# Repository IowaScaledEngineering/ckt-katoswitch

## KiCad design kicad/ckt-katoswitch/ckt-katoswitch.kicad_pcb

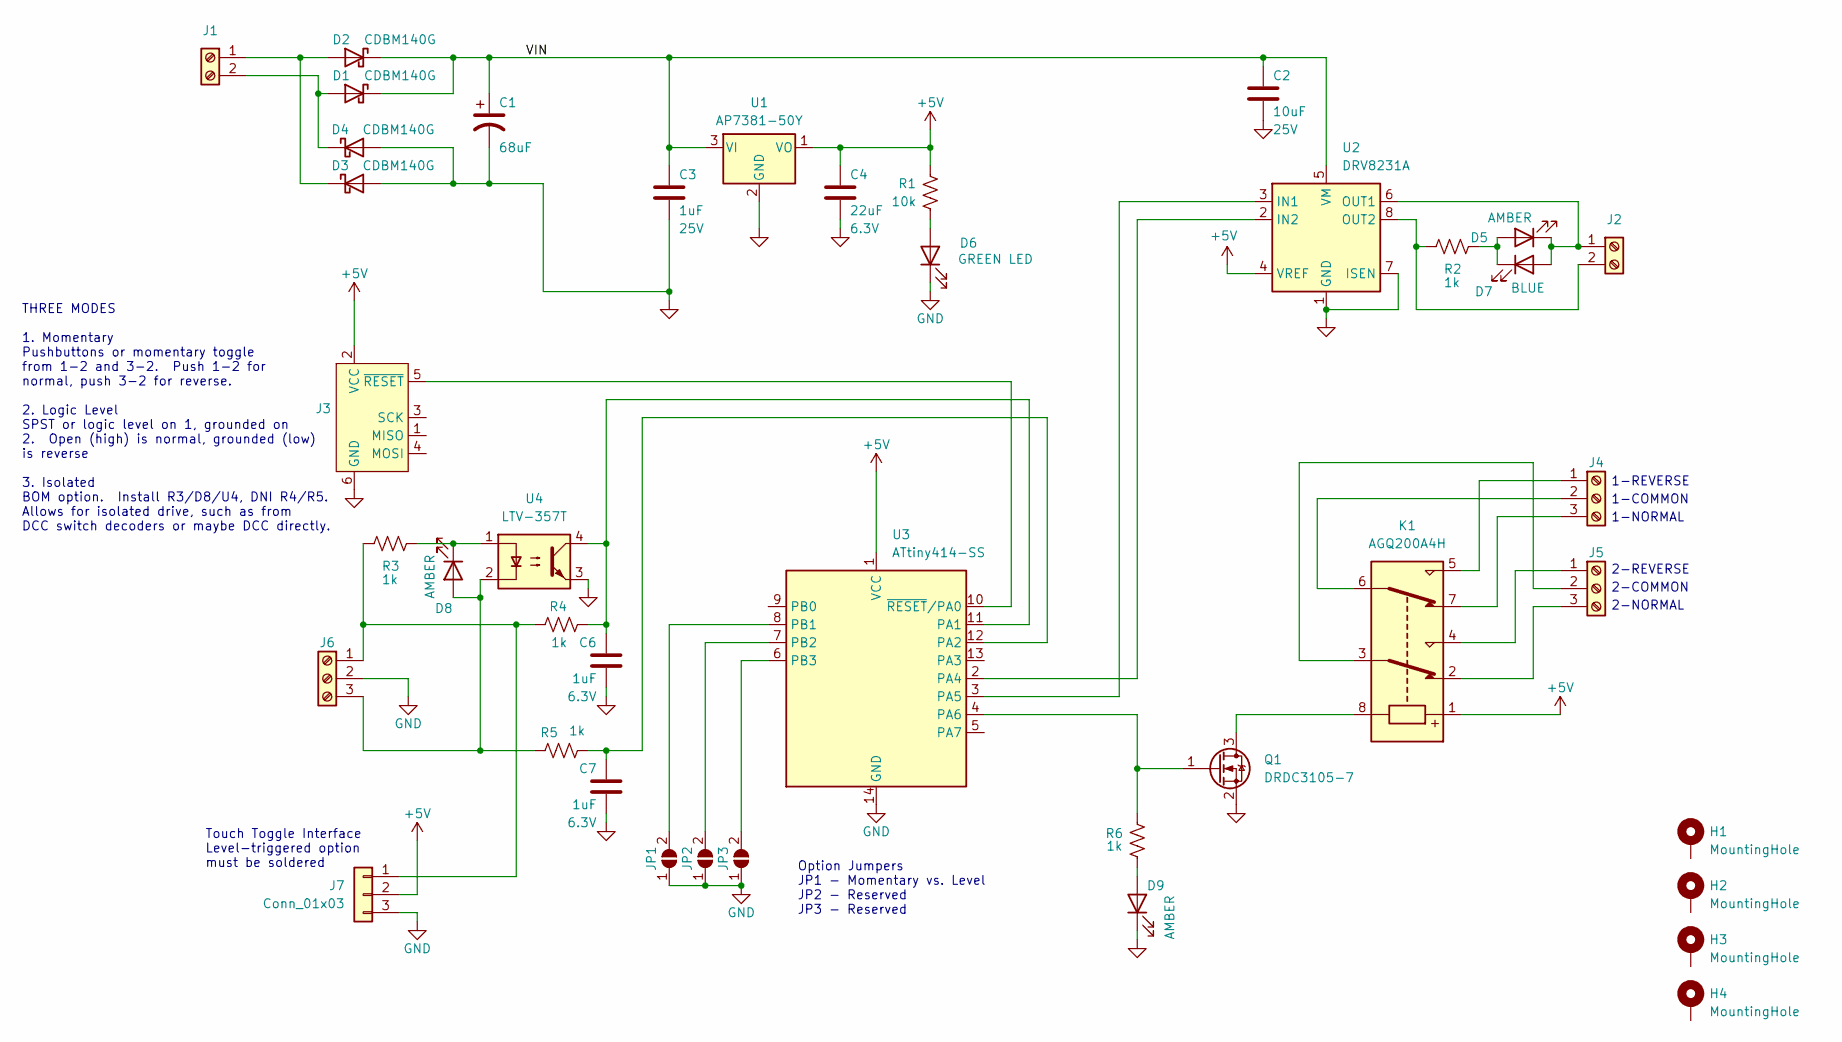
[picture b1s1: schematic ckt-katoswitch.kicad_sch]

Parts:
C1: 68uF; CP_Elec_6.3x5.8
C2: 10uF; C_0805_2012Metric; Voltage 25V
C3: 1uF; C_0805_2012Metric; Voltage 25V
C4: 22uF; C_0805_2012Metric; Voltage 6.3V
C6, C7: 1uF; C_0805_2012Metric; Voltage 6.3V
D1, D2, D3, D4: CDBM140G; SOD-123T
D5, D8, D9: AMBER; LED_0805_2012Metric
D6: GREEN LED; LED_0805_2012Metric
D7: BLUE; LED_0805_2012Metric
H1, H2, H3, H4: MountingHole; MountingHole_3.2mm_M3_Pad
J1, J2: Screw_Terminal_01x02; TerminalBlock_RND_205-00012_1x02_P5.00mm_Horizontal
J3: Conn_AVR_TagConnect_TC2030; Tag-Connect_TC2030-IDC-NL_2x03_P1.27mm_Vertical
J4, J5, J6: Screw_Terminal_01x02; TerminalBlock_MetzConnect_Type059_RT06303HBWC_1x03_P3.50mm_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
J7: Conn_01x03; PinHeader_1x03_P2.54mm_Vertical
JP1, JP2, JP3: SolderJumper_2_Open; SolderJumper-2_P1.3mm_Open_RoundedPad1.0x1.5mm
K1: AGQ200A4H; RELAY_AGQ_A_PAN
Q1: DRDC3105-7; SOT-23
R1: 10k; R_0805_2012Metric
R2, R3, R4, R5, R6: 1k; R_0805_2012Metric
U1: AP7381-50Y; SOT-89-3
U2: DRV8231A; Texas_HTSOP-8-1EP_3.9x4.9mm_P1.27mm_EP2.95x4.9mm_Mask2.4x3.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
U3: ATtiny414-SS; SOIC-14_3.9x8.7mm_P1.27mm
U4: LTV-357T; SO-4_4.4x3.6mm_P2.54mm

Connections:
+5V: C4.1, J3.2 (VCC), J7.2, K1.1, R1.2, U1.1 (VO), U2.4 (VREF), U3.1 (VCC)
/VIN: C1.1, C2.1, C3.1, D1.1 (K), D2.1 (K), U1.3 (VI), U2.5 (VM)
GND: C1.2, C2.2, C3.2, C4.2, C6.2, C7.2, D3.2 (A), D4.2 (A), D6.1 (K), D9.1 (K), J3.6 (GND), J6.2, J7.3, JP1.1 (A), JP2.1 (A), JP3.1 (A), Q1.2 (S), U1.2 (GND), U2.1 (GND), U2.7 (ISEN), U2.9 (GND), U3.14 (GND), U4.3
unnamed: D1.2 (A), D4.1 (K), J1.2
unnamed: D2.2 (A), D3.1 (K), J1.1
unnamed: D5.2 (A), D7.1 (K), R2.1
unnamed: D5.1 (K), D7.2 (A), J2.1, U2.6 (OUT1)
unnamed: D6.2 (A), R1.1
unnamed: D8.2 (A), J6.3, R5.2, U4.2
unnamed: D8.1 (K), R3.1, U4.1
unnamed: D9.2 (A), R6.2
unnamed: J2.2, R2.2, U2.8 (OUT2)
unnamed: J3.5 (~RESET), U3.10 (~RESET/PA0)
unnamed: J4.1, K1.5
unnamed: J4.2, K1.6
unnamed: J4.3, K1.7
unnamed: J5.1, K1.4
unnamed: J5.2, K1.3
unnamed: J5.3, K1.2
unnamed: J6.1, J7.1, R3.2, R4.2
unnamed: JP1.2 (B), U3.8 (PB1)
unnamed: JP2.2 (B), U3.7 (PB2)
unnamed: JP3.2 (B), U3.6 (PB3)
unnamed: K1.8, Q1.3 (D)
unnamed: Q1.1 (G), R6.1, U3.4 (PA6)
unnamed: U2.3 (IN1), U3.3 (PA5)
unnamed: U2.2 (IN2), U3.2 (PA4)
unnamed: C6.1, R4.1, U3.11 (PA1), U4.4
unnamed: C7.1, R5.1, U3.12 (PA2)

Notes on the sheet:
1-NORMAL
2-COMMON
2-NORMAL
1-COMMON
THREE MODES 1. Momentary Pushbuttons or momentary toggle from 1-2 and 3-2. Push 1-2 for normal, push 3-2 for reverse. 2. Logic Level SPST or logic level on 1, grounded on 2. Open (high) is normal, grounded (low) is reverse 3. Isolated BOM option. Install R3/D8/U4, DNI R4/R5. Allows for isolated dri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
Option Jumpers JP1 - Momentary vs. Level JP2 - Reserved JP3 - Reserved
1-REVERSE
2-REVERSE
Touch Toggle Interface Level-triggered option must be soldered

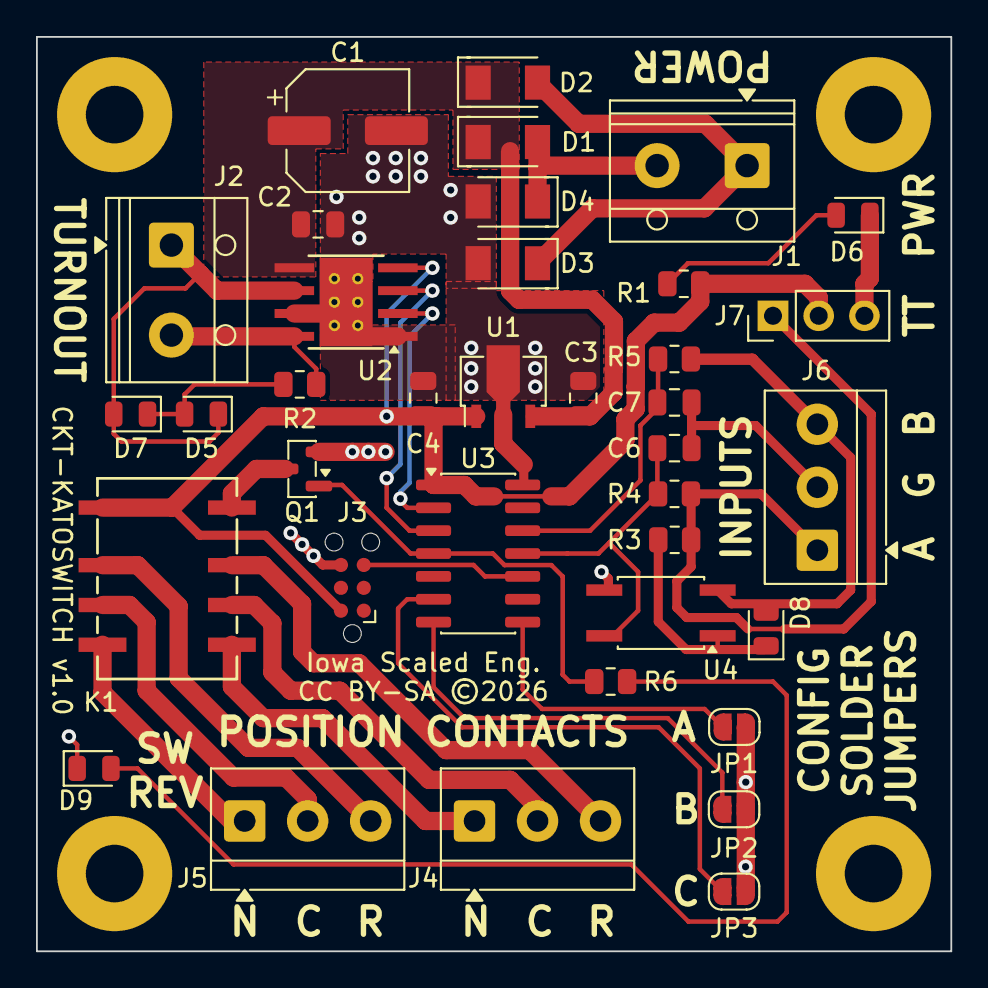
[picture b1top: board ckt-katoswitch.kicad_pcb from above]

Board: 2 copper layers, 50.8 x 50.8 mm, 41 parts (0 on the bottom side), 29 nets.

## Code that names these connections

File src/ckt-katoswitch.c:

/*************************************************************************
Title:    CKT-KATOSWITCH
Authors:  Michael Petersen <railfan@drgw.net>
          Nathan D. Holmes <maverick@drgw.net>
File:     $Id: $
License:  GNU General Public License v3

LICENSE:
    Copyright (C) 2026 Michael Petersen & Nathan Holmes

    This program is free software; you can redistribute it and/or modify
    it under the terms of the GNU General Public License as published by
    the Free Software Foundation; either version 3 of the License, or
    any later version.

    This program is distributed in the hope that it will be useful,
    but WITHOUT ANY WARRANTY; without even the implied warranty of
    MERCHANTABILITY or FITNESS FOR A PARTICULAR PURPOSE.  See the
    GNU General Public License for more details.

*************************************************************************/

#include <util/delay.h>
#include <avr/io.h>
#include <avr/interrupt.h>
#include <avr/cpufunc.h> // For ccp_write_io()
#include <util/delay.h>
#include <stdint.h>
#include <stdbool.h>
#include <avr/wdt.h>
#include "debouncer.h"
#include "eepromWearLevel.h"


WearLeveledEEPROM stateSaveEEP;
#define WL_EEPROM_SIZE  63
#define WL_EEPROM_START_ADDR 0

FUSES = 
{
    .OSCCFG = FREQSEL_16MHZ_gc,
};
 
void init_1000hz_tick(void) 
{
	/*
	* Timing calculation:
	* Clock Source: CLK_PER / 2 = 8,000,000 / 2 = 4,000,000 Hz (4 MHz)
	* Desired Interrupt Rate: 1000 Hz (1 ms)
	* 
	* TOP (CCMP) = (f_clk / Target_Freq) - 1
	* TOP = (4,000,000 / 1000) - 1 = 3999
	*/
	TCB0.CCMP = 3999;

	/* Set mode to Periodic Interrupt mode (default is 0x00, but explicit here) */
	TCB0.CTRLB = TCB_CNTMODE_INT_gc;

	/* Enable Capture/Compare interrupt */
	TCB0.INTCTRL = TCB_CAPT_bm;

	/*
	* Configure Clock Source and Enable:
	* - TCB_CLKSEL_CLKDIV2_gc: Use CLK_PER / 2 (4 MHz)
	* - TCB_ENABLE_bm: Enable the timer
	*/
	TCB0.CTRLA = TCB_CLKSEL_CLKDIV2_gc | TCB_ENABLE_bm;
}

volatile bool systick = false;

ISR(TCB0_INT_vect) 
{
	/* Clear the interrupt flag */
	TCB0.INTFLAGS = TCB_CAPT_bm;
	systick = true;
}
 
void init_clock(void) 
{
    _PROTECTED_WRITE(CLKCTRL.MCLKCTRLB, CLKCTRL_PEN_bm | CLKCTRL_PDIV_2X_gc);

    /* 3. Wait for oscillator to stabilize */
    while (CLKCTRL.MCLKSTATUS & CLKCTRL_SOSC_bm);
}

void init_gpio(void) 
{
	// PORT A
	//  PA7 - Output - no connection, drive low
	//  PA6 - Output - Relay (high = reverse)
	//  PA5 - Output - DRV8231A IN1
	//  PA4 - Output - DRV8231A IN2
	//  PA3 - Output - no connection, drive low
	//  PA2 - Input  - Input B
	//  PA1 - Input  - Input A
	//  PA0 - UPDI   - Reset/programming pin

	// PORT B
	//  PA3 - Input  - Option Jumper C
	//  PA2 - Input  - Option Jumper B
	//  PA1 - Input  - Option Jumper A
	//  PB0 - Output - no connection, drive low

	// Initial pin states for outputs 
	PORTA.OUTCLR = PIN7_bm | PIN6_bm | PIN5_bm | PIN4_bm | PIN3_bm;
	PORTB.OUTCLR = PIN0_bm;

	// Outputs are set, inputs are clr in the DIR register
	PORTA.DIRSET = PIN7_bm | PIN6_bm | PIN5_bm | PIN4_bm | PIN3_bm;
	PORTB.DIRSET = PIN0_bm;
	
	// PORTA Pins 1 & 2 are the inputs
	PORTA.DIRCLR = PIN2_bm | PIN1_bm;
	PORTB.DIRCLR = PIN1_bm | PIN2_bm | PIN3_bm;

	// Turn on pull-ups and invert all the inputs since they're active low
	PORTA.PIN2CTRL = PORT_PULLUPEN_bm | PORT_INVEN_bm;
	PORTA.PIN1CTRL = PORT_PULLUPEN_bm | PORT_INVEN_bm;
	PORTB.PIN3CTRL = PORT_PULLUPEN_bm | PORT_INVEN_bm;
	PORTB.PIN2CTRL = PORT_PULLUPEN_bm | PORT_INVEN_bm;
	PORTB.PIN1CTRL = PORT_PULLUPEN_bm | PORT_INVEN_bm;
}

void init()
{
	init_clock();
	init_gpio();
	init_1000hz_tick();
	sei();

	ewlInit(&stateSaveEEP, (const uint8_t*)WL_EEPROM_START_ADDR, WL_EEPROM_SIZE * (sizeof(uint8_t)+1), sizeof(uint8_t));	
};

#define SWITCH_A_MASK  PIN1_bm
#define SWITCH_B_MASK  PIN2_bm

uint8_t getInputs()
{
	return (PORTA.IN & (PIN2_bm | PIN1_bm));
}

#define OPTION_A_MASK  PIN1_bm
#define OPTION_B_MASK  PIN2_bm
#define OPTION_C_MASK  PIN3_bm

uint8_t getOptionJumpers()
{
	return (PORTB.IN & (PIN3_bm | PIN2_bm | PIN1_bm));
}
#define SWITCH_READ_TIME_MS  25
#define COIL_ON_TIME_MS      600

#define STATE_NORMAL  0x01
#define STATE_REVERSE 0x02


// Returns true if the coil is active (points moving) or false if the coil is idle

void setRelayReverse(bool isReverse)
{
	if (isReverse)
		PORTA.OUTSET = PIN6_bm;
	else
		PORTA.OUTCLR = PIN6_bm;
}

bool operateCoilDriver(bool setNormal, bool setReverse, uint16_t currentMillis)
{
	static uint16_t coilDriverStarted = 0;
	static uint8_t currentState = 0;

	if (!(PORTA.OUT & (PIN4_bm | PIN5_bm)))
	{
		// Coil is inactive
		if (setNormal)
		{
			PORTA.OUTSET = PIN5_bm;
			PORTA.OUTCLR = PIN4_bm;
			coilDriverStarted = currentMillis;
			return true;
		}
		else if (setReverse)
		{
			PORTA.OUTSET = PIN4_bm;
			PORTA.OUTCLR = PIN5_bm;
			coilDriverStarted = currentMillis;
			return true;
		}

		return false;
	}


	// If we're here, the coil is active
	if (currentMillis - coilDriverStarted > COIL_ON_TIME_MS)
	{
		// Don't change the relay until we finish the throw
		if (PORTA.OUT & PIN4_bm)
		{
			currentState = STATE_REVERSE;
		} else if (PORTA.OUT & PIN5_bm) {
			currentState = STATE_NORMAL;
		}
		// Shut coil off
		PORTA.OUTCLR = PIN5_bm | PIN4_bm;
		setRelayReverse(STATE_REVERSE == currentState);

		return false;
	}
	return true;
}



bool isButtonTriggered(uint8_t options)
{
	if (options & OPTION_A_MASK)
		return false;
		
	return true;
}

bool isLevelTriggered(uint8_t options)
{
	return !isButtonTriggered(options);
}


int main(void) 
{
	DebounceState8_t inputDebouncer;
	uint16_t lastInputRead = 0;
	uint8_t optionJumpers = 0;
	uint8_t currentState = 0;
	uint16_t millis = 1;

	wdt_enable(WDTO_120MS);

	init();

	_delay_ms(10); // Just wait for everything to stabilize electrically

	initDebounceState8(&inputDebouncer, getInputs());

	// This doesn't need to be debounced.  They're solder jumpers, don't change them
	//  at runtime with the power on
	optionJumpers = getOptionJumpers();



	if (isButtonTriggered(optionJumpers) && ewlRead(&stateSaveEEP, (const uint8_t*)&currentState, sizeof(uint8_t)))
	{
		// Only do this if we're in pushbutton mode
		// Level-triggered doesn't need state-saving
		// Set up current state based on state on power loss
		
		if (STATE_REVERSE == currentState)
		{
			operateCoilDriver(false, true, millis);
			setRelayReverse(true); // set relay immediately since we're restoring state
		} else if (STATE_NORMAL == currentState) {
			operateCoilDriver(true, false, millis);
			setRelayReverse(false); // set relay immediately since we're restoring state
		}
	}
	
	while (1) 
	{
		if (systick)
		{
			systick = false;
			millis++;
		}

		wdt_reset();

		bool isPointsMoving = operateCoilDriver(false, false, millis);

		if (!isPointsMoving && (millis - lastInputRead > SWITCH_READ_TIME_MS))
		{
			uint8_t changed = debounce8(getInputs(), &inputDebouncer);
			lastInputRead = millis;

			uint8_t buttonsPressed = getDebouncedState(&inputDebouncer);

			// Different modes
			// Mode 0 is toggle switch - A is level sensitive
			// Mode 1 is pushbuttons - A is normal, B is reverse
			uint8_t newState = 0;
			if (isButtonTriggered(optionJumpers))
			{
				buttonsPressed = buttonsPressed & changed;
				if (buttonsPressed & SWITCH_A_MASK)
				{
					newState = STATE_NORMAL;
				} else if (buttonsPressed & SWITCH_B_MASK) {
					newState = STATE_REVERSE;
				}
			}
			else if (isLevelTriggered(optionJumpers))
			{
				// Level sensitive mode
				if (buttonsPressed & SWITCH_A_MASK)
					newState = STATE_REVERSE;
				else
					newState = STATE_NORMAL;				
			}

			if (0 != newState && newState != currentState)
			{
				bool setNormal = (newState == STATE_NORMAL);
				bool setReverse = (newState == STATE_REVERSE);
				currentState = newState;
				// State saving is only needed on button triggering, don't waste eep cycles if we don't need it
				if (isButtonTriggered(optionJumpers))
					ewlWrite(&stateSaveEEP, (const uint8_t*)&currentState, sizeof(uint8_t));
				operateCoilDriver(setNormal, setReverse, millis);
			}
		}
	}
	return 0;
}

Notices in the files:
kicad/ckt-katoswitch/ckt-katoswitch.kicad_pcb:
CC BY-SA ©2026
